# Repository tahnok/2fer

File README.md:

# 2FER

```
________________________________________
\_____  \_   _____/\_   _____/\______   \
 /  ____/|    __)   |    __)_  |       _/
/       \|     \    |        \ |    |   \
\_______ \___  /   /_______  / |____|_  /
        \/   \/            \/         \/
```

A 2 key keyboard for cherry mx switches in the featherwing form factor

Runs (hopefully) QMK firmware, over at this branch: https://github.com/tahnok/qmk_firmware/tree/2fer

3D models from https://github.com/ktec-hq/kicad-library

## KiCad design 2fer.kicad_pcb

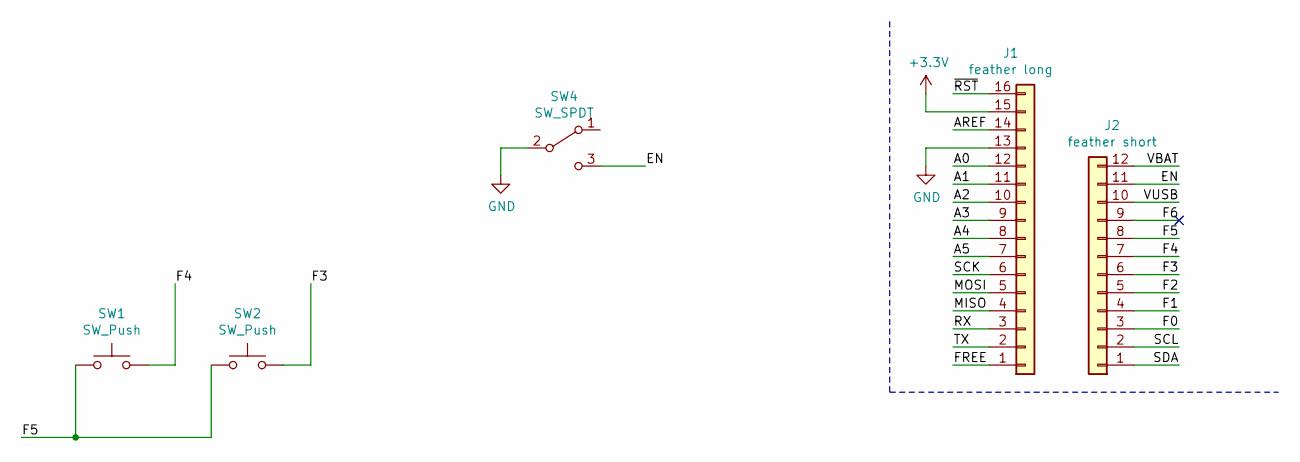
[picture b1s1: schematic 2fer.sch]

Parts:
J1: feather long; PinHeader_1x16_P2.54mm_Vertical
J2: feather short; PinHeader_1x12_P2.54mm_Vertical
SW1, SW2: SW_Push; SW_Cherry_MX_1.00u_PCB
SW4: SW_SPDT; Switch-SPST_CSS-1210MC

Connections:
+3V3: J1.15
/A0: J1.12
/A1: J1.11
/A2: J1.10
/A3: J1.9
/A4: J1.8
/A5: J1.7
/AREF: J1.14
/EN: J2.11, SW4.3 (C)
/F0: J2.3
/F1: J2.4
/F2: J2.5
/F3: J2.6, SW2.2
/F4: J2.7, SW1.2
/F5: J2.8, SW1.1, SW2.1
/F6: J2.9
/FREE: J1.1
/MISO: J1.4
/MOSI: J1.5
/RX: J1.3
/SCK: J1.6
/SCL: J2.2
/SDA: J2.1
/TX: J1.2
/VBAT: J2.12
/VUSB: J2.10
/~RST: J1.16
GND: J1.13, SW4.2 (B)

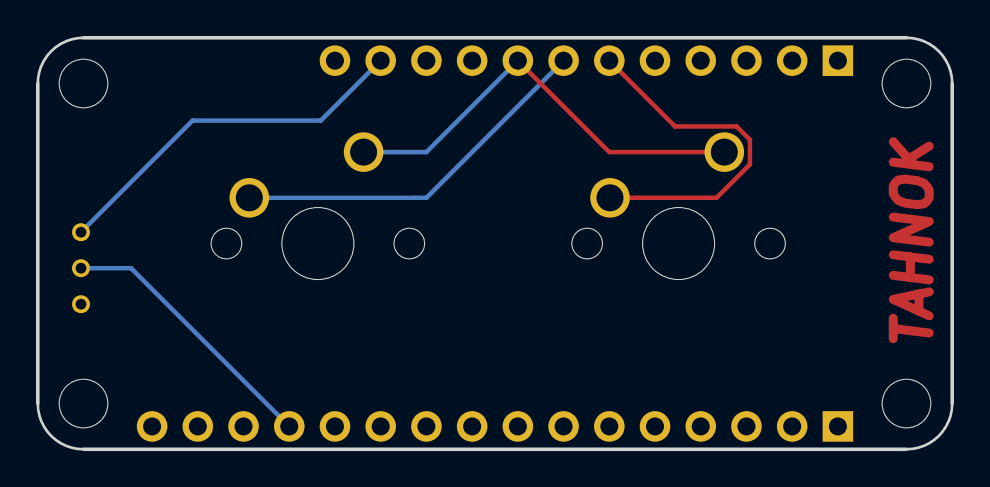
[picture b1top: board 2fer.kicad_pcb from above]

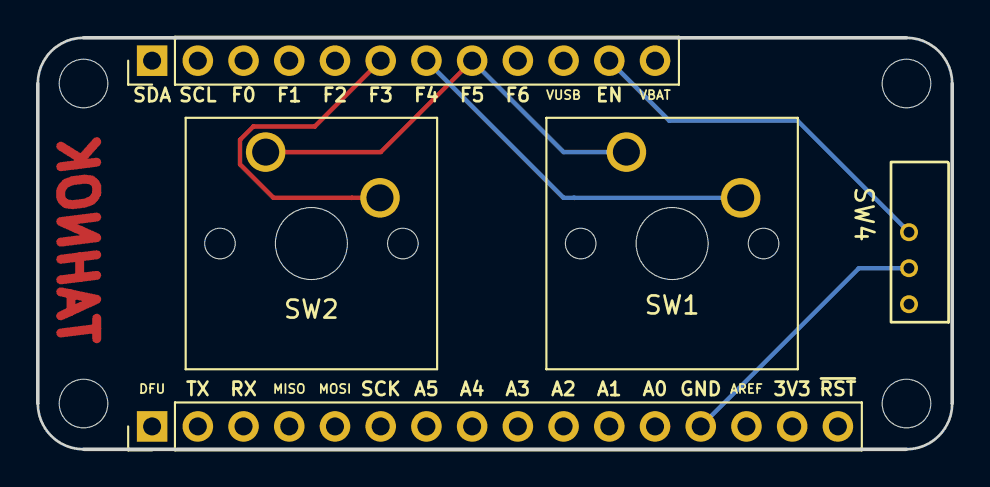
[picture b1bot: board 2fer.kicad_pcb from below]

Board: 2 copper layers, 50.8 x 22.9 mm, 5 parts (3 on the bottom side), 5 nets.

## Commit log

2020-01-11 initial
2020-01-12 Revision 1
